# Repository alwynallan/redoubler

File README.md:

# REDOUBLER

REDOUBLER is a Random Number Generator based on Modular Entropy Multiplication. It is Open Source Hardware. The device plugs into a host's USB port, and enumerates as a standard microphone. When the microphone is sampled it produces white noise which contains a high proportion of random entropy. The digital data behind that white noise is random numbers, and they can be recorded and used for any purpose that requires a non-deterministic entropy source.

By enumerating as a standard USB microphone (sound card with one input) REDOUBLER does not require drivers on any major operating system. This simplifies development, and reduces the "attack surface" that an adversary can use to compromise security. Moreover, the data paths used by microphones are highly optimized for efficiency.

### Modular Entropy Multiplication

Non-deterministic random number generators use various methods to gather entropy. Avalanche noise from reverse-biased semiconductor junctions is popular, but others include video of Lava Lamps, radios tuned away from stations, quantum effects, digital logic race conditions, and radioactive decay events. Modular Entropy Multiplication (MEM) is a new method.

Invented by the author, [Peter Allan], in the late 1990's and independently by Bill Cox in the early 2010's, MEM repeatedly compares a voltage with the midpoint of its range, then doubles either the voltage or excess over the midpoint as appropriate, and stores the result. Depending on the comparison, either a '0' or a '1' bit is output.

As a circuit, the analog part of MEM looks like this

The Track and Holds store the voltages, one for the source voltage and one for the result. The Comparators compare the stored voltages with the midpoint of their range, and produce a digital output based on the result. The Opamps double the input voltage and, depending on the result of the comparison, shift it by the voltage range. The clocks q and qp are symmetric and non-overlapping and control the pace of the circuit, while the output bits are collected at c0 and c1. When recorded over time, the analog voltages have characteristic time traces like this.

In the REDOUBLER, all of the components except the resistors are reconfigurable analog blocks on a Cypress Semiconductor PSoC 5LP chip. It has two such generators operating simultaneously at 768,000 bps, for a combined output of 1,536,000 bps. The bit-stream has about 7.9 bits/byte of entropy, and is not whitened, leaving the host to apply a whitening filter if required. Here is one second worth of data as an image (click twice to see it full-scale).

Modular Entropy Multiplication has advantages over all other methods because it is simultaneously simple, efficient, fast, and robust. It uses common components, used within their specified ranges. It is amenable to implementation on silicon, and has proven resistant to external electrical influence, even when unshielded. Bill and I hope that REDOUBLER and his [Infinite Noise TRNG] are just the beginning for this method, and we have disclaimed any patent rights to the technology.

### The Circuit

The REDOUBLER circuit is designed in the latest free version of CadSoft Eagle and files are in the [circuit](circuit) branch of this repository.

The PSoC chip contains both reconfigurable analog components and digital logic, so the only components unique to REDOUBLER are the eight resistors at top-right.

A Bill Of Materials is also disclosed. Boards are available from [OSH Park].

### The Firmware

The firmware for REDOUBLER is written in the highly integrated and free-to-use [Cypress PSoC Creator] development environment. The source code is in the [psoc_creator_firmware](psoc_creator_firmware) branch of this repository. I highly recommend this toolchain and microcontroller product line. The current state of the firmware source is efficient and reliable, but a little rough looking. The USB audio functions were culled from an [example project], and much of that code remains in comments.

Once the firmware is built, it can be programmed onto a REDOUBLER using the $90 [MiniProg3](http://www.cypress.com/?rID=38154) or the left portion of the $10 [CY8CKIT-059](http://www.cypress.com/?rid=108038). [Pogo Pins] are useful for connecting to the 5 pads on the REDOUBLER board.

REDOUBLER uses a USB product ID granted by [openmoko.org].

### Host Software

As open source software, users are asked to contribute their developments back to this repository. For now support is sparse. Anything that can be done with a USB microphone can be done with REDOUBLER. [Linux](host_linux) is likely to be best supported, but [Windows](host_windows) and Mac [OS-X](host_osx) will have branches here too. Audacity runs on all three platforms, and can be used to record, view, manipulate and save data from REDOUBLER, so we know everything's possible.

Ultimately the goal is for REDOUBLER to be plugged into any flavor of machine, and have the operating system's random number generator immediately enhanced with copious high-quality entropy.

[Peter Allan]: mailto:alwynallan@gmail.com
[Infinite Noise TRNG]: https://github.com/waywardgeek/infnoise
[Cypress PSoC Creator]: http://www.cypress.com/psoccreator/
[Pogo Pins]: https://www.sparkfun.com/products/9174
[example project]: http://www.element14.com/community/thread/28830/l/psoc-4-pioneer-kit-community-project102-usb-audio-using-the-psoc-5lp?displayFullThread=true
[OSH park]: https://oshpark.com/shared_projects/GZnEjhlQ
[openmoko.org]: http://wiki.openmoko.org/wiki/USB_Product_IDs

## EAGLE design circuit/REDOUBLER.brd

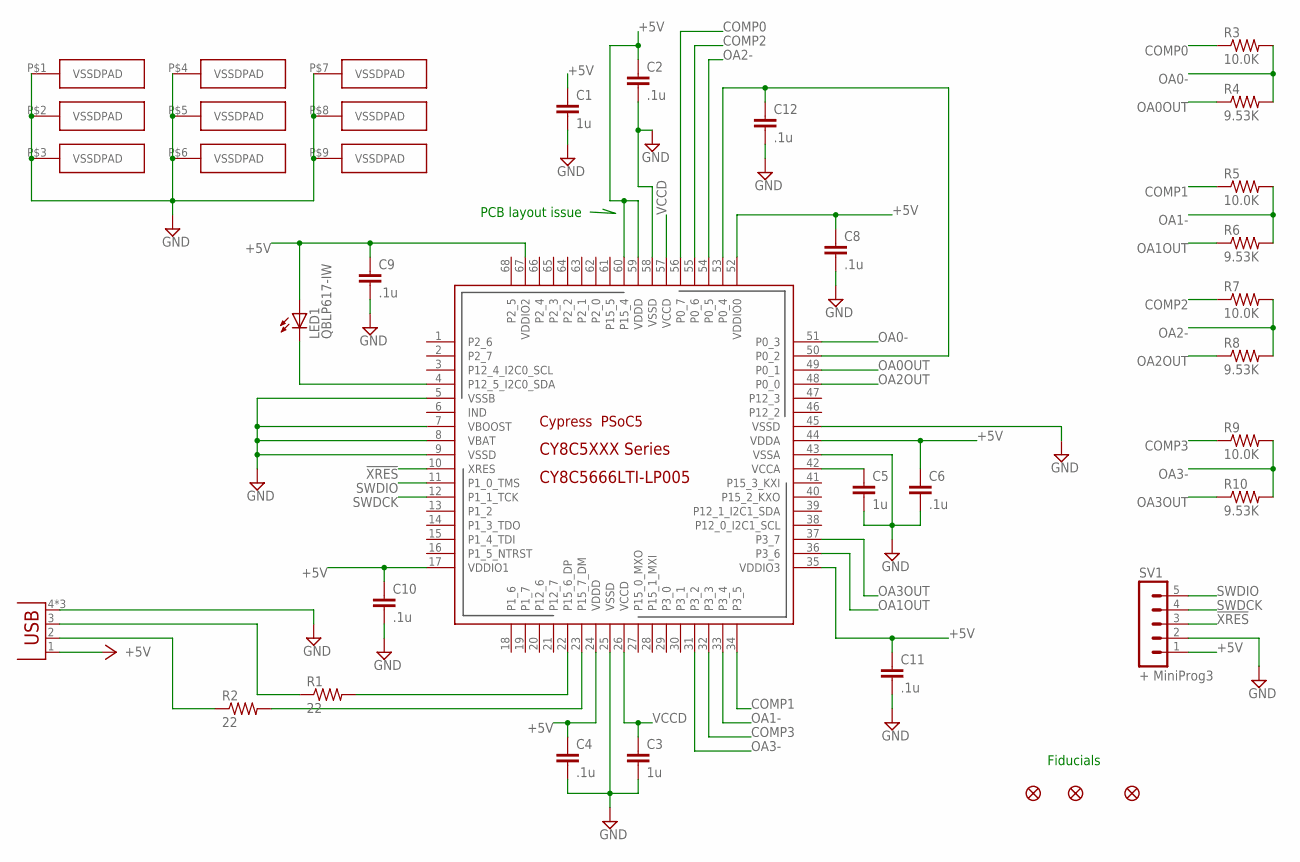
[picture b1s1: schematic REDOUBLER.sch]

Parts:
C1, C3, C5: 1u; C0402
C2, C4, C6, C8, C9, C10, C11, C12: .1u; C0402
FID1, FID2, FID3: FIDUCIALUFIDUCIAL; MICRO-FIDUCIAL
LED1: QBLP617-IW; CHIP-LED0603
R1, R2: 22; R0402
R3, R5, R7, R9: 10.0K; R0402
R4, R6, R8, R10: 9.53K; R0402
SV1: + MiniProg3; MA05-1
U$1: CY8C5666LTI-LP005; QFN68
X1: USBSMT-MALE; USB-A-SMT-MALE

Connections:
!XRES!: SV1.3, U$1.10 (XRES)
+5V: C1.1, C2.1, C4.1, C6.1, C8.1, C9.1, C10.1, C11.1, LED1.A, SV1.1, U$1.17 (VDDIO1), U$1.24 (VDDD), U$1.35 (VDDIO3), U$1.44 (VDDA), U$1.52 (VDDIO0), U$1.59 (VDDD), U$1.60 (P15_4), U$1.67 (VDDIO2), X1.1 (VCC)
COMP0: R3.1, U$1.56 (P0_7)
COMP1: R5.1, U$1.34 (P3_5)
COMP2: R7.1, U$1.55 (P0_6)
COMP3: R9.1, U$1.32 (P3_3)
GND: C1.2, C2.2, C3.2, C4.2, C5.2, C6.2, C8.2, C9.2, C10.2, C11.2, C12.2, SV1.2, U$1.5 (VSSB), U$1.7 (VBOOST), U$1.8 (VBAT), U$1.9 (VSSD), U$1.25 (VSSD), U$1.43 (VSSA), U$1.45 (VSSD), U$1.58 (VSSD), U$1.P$1 (VSSDPAD), U$1.P$2 (VSSDPAD), U$1.P$3 (VSSDPAD), U$1.P$4 (VSSDPAD), U$1.P$5 (VSSDPAD), U$1.P$6 (VSSDPAD), U$1.P$7 (VSSDPAD), U$1.P$8 (VSSDPAD), U$1.P$9 (VSSDPAD), X1.4 (GND), X1.P$1 (GND), X1.P$3 (GND)
unnamed: C12.1, U$1.50 (P0_2), U$1.53 (P0_4)
unnamed: LED1.C, U$1.4 (P12_5_I2C0_SDA)
unnamed: R1.1, X1.3 (D+)
unnamed: R2.1, X1.2 (D-)
unnamed: R1.2, U$1.22 (P15_6_DP)
unnamed: R2.2, U$1.23 (P15_7_DM)
unnamed: C5.1, U$1.42 (VCCA)
OA0-: R3.2, R4.2, U$1.51 (P0_3)
OA0OUT: R4.1, U$1.49 (P0_1)
OA1-: R5.2, R6.2, U$1.33 (P3_4)
OA1OUT: R6.1, U$1.36 (P3_6)
OA2-: R7.2, R8.2, U$1.54 (P0_5)
OA2OUT: R8.1, U$1.48 (P0_0)
OA3-: R9.2, R10.2, U$1.31 (P3_2)
OA3OUT: R10.1, U$1.37 (P3_7)
SWDCK: SV1.4, U$1.12 (P1_1_TCK)
SWDIO: SV1.5, U$1.11 (P1_0_TMS)
VCCD: C3.1, U$1.26 (VCCD), U$1.57 (VCCD)

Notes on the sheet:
Fiducials
PCB layout issue

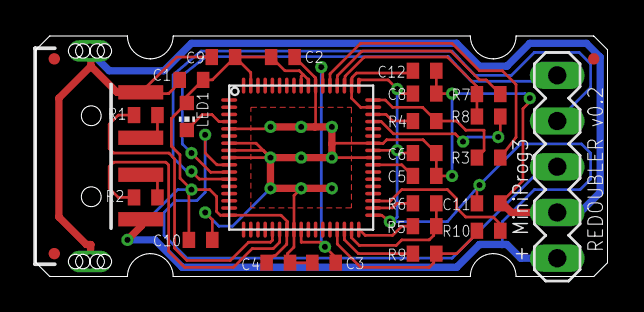
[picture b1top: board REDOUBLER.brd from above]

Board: 2 copper layers, 31.8 x 13.4 mm, 28 parts (0 on the bottom side), 25 nets.

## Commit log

2015-03-05 added the psoc_creator_firmware directory
2015-03-07 Streamline PSoC 5 Firmware
2015-03-07 Update Do_not_update_USBFS_component!
2015-03-07 minor edits
2015-03-07 Added images
2015-03-07 Cleanup
2015-03-07 New image
2015-03-08 Further simplified firmware
2015-03-08 Firmware work
2015-03-08 Clean firmware
2015-03-08 Added traces image
2015-03-08 Added circuit
2015-03-08 Fixed circuit images
2015-03-08 Added LICENSE
2015-03-08 added host_linux files
2015-03-08 added host-windows
2015-03-08 Mac stub added
2015-03-09 Fix firmware issue.
2015-03-10 Fixed USBFS update issue
2015-03-10 USBFS_episr.c cleanup
2015-03-11 added whiten pipe
2015-03-11 Format a comment
2015-03-11 Cleaned whiten
2015-03-14 added runs
2015-03-19 added whiten options and VID/PID
2015-03-20 whiten help & leave .hex
2015-03-27 added xorbits and auto USB voltage detect
2015-04-02 Fixed runs to give same result as pipe
2015-04-06 added bang32.c

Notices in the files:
circuit/REDOUBLER.brd:
Copyright (C) 2015 Peter Allan
parts and their libraries:
SparkFun-Aesthetics: Licensing: Creative Commons ShareAlike 4.0 International - https://creativecommons.org/licenses/by-sa/4.0
PatternAgents-Cypress: License : http://creativecommons.org/licenses/by-sa/3.0
(Creative Commons 3.0)
